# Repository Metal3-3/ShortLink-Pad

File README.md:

# ShortLink-Pad

A hackpad mainly for links and easy accses. Consists of 5 keyswiches 1 rotary encoder for volume controll and ect, one 0.91 inch oled and seeeduino xiao for the micro controller.

# PCB design

it has been designed in kicad and i used the libraries from the guide.

# CAD design

it has been designed in tinkercad and uses m3 screws (3.4mm) might turn out different with other printers
The link: https://www.tinkercad.com/things/gyOfBtvMFHk-hack-pad

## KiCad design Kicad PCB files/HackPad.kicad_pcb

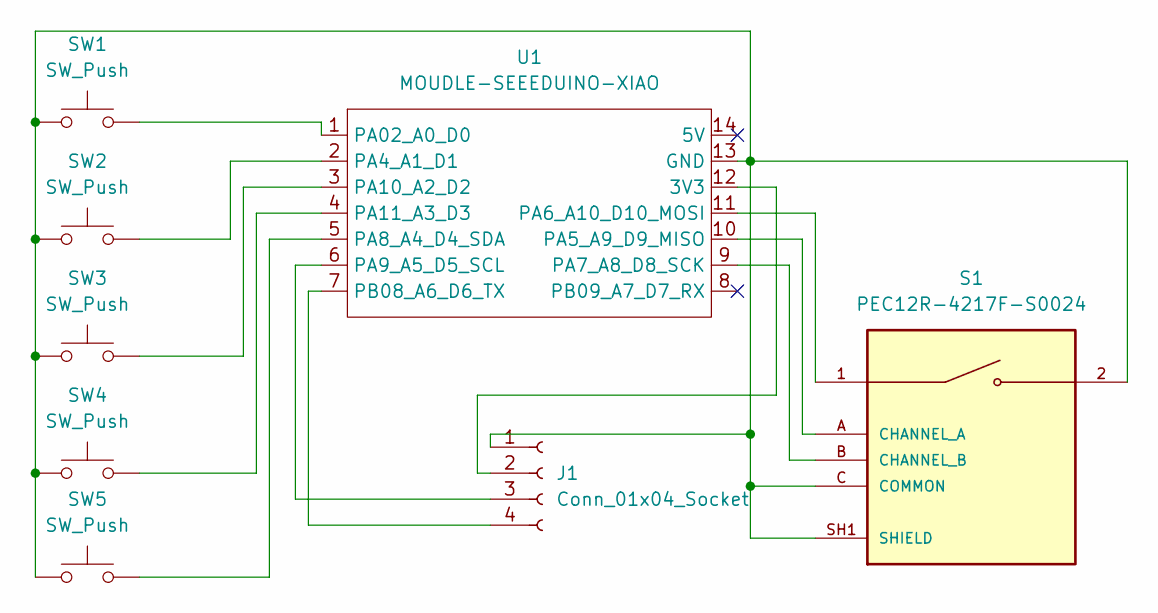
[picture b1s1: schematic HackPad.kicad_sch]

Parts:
J1: Conn_01x04_Socket; SSD1306-0.91-OLED-4pin-128x32
S1: PEC12R-4217F-S0024; XDCR_PEC12R-4217F-S0024; PARTREV 07/21
SW1, SW2, SW3, SW4, SW5: SW_Push; MX-Solderable-1U
U1: MOUDLE-SEEEDUINO-XIAO; XIAO-SAMD21-SMD

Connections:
unnamed: J1.1, S1.2, S1.C (COMMON), S1.SH1 (SHIELD), S1.SH2 (SHIELD), SW1.1, SW2.1, SW3.1, SW4.1, SW5.1, U1.13 (GND)
unnamed: J1.2, U1.12 (3V3)
unnamed: J1.3, U1.6 (PA9_A5_D5_SCL)
unnamed: J1.4, U1.7 (PB08_A6_D6_TX)
unnamed: S1.A (CHANNEL_A), U1.10 (PA5_A9_D9_MISO)
unnamed: S1.B (CHANNEL_B), U1.9 (PA7_A8_D8_SCK)
unnamed: SW1.2, U1.1 (PA02_A0_D0)
unnamed: SW2.2, U1.2 (PA4_A1_D1)
unnamed: S1.1, U1.11 (PA6_A10_D10_MOSI)
unnamed: SW5.2, U1.5 (PA8_A4_D4_SDA)
unnamed: SW3.2, U1.3 (PA10_A2_D2)
unnamed: SW4.2, U1.4 (PA11_A3_D3)

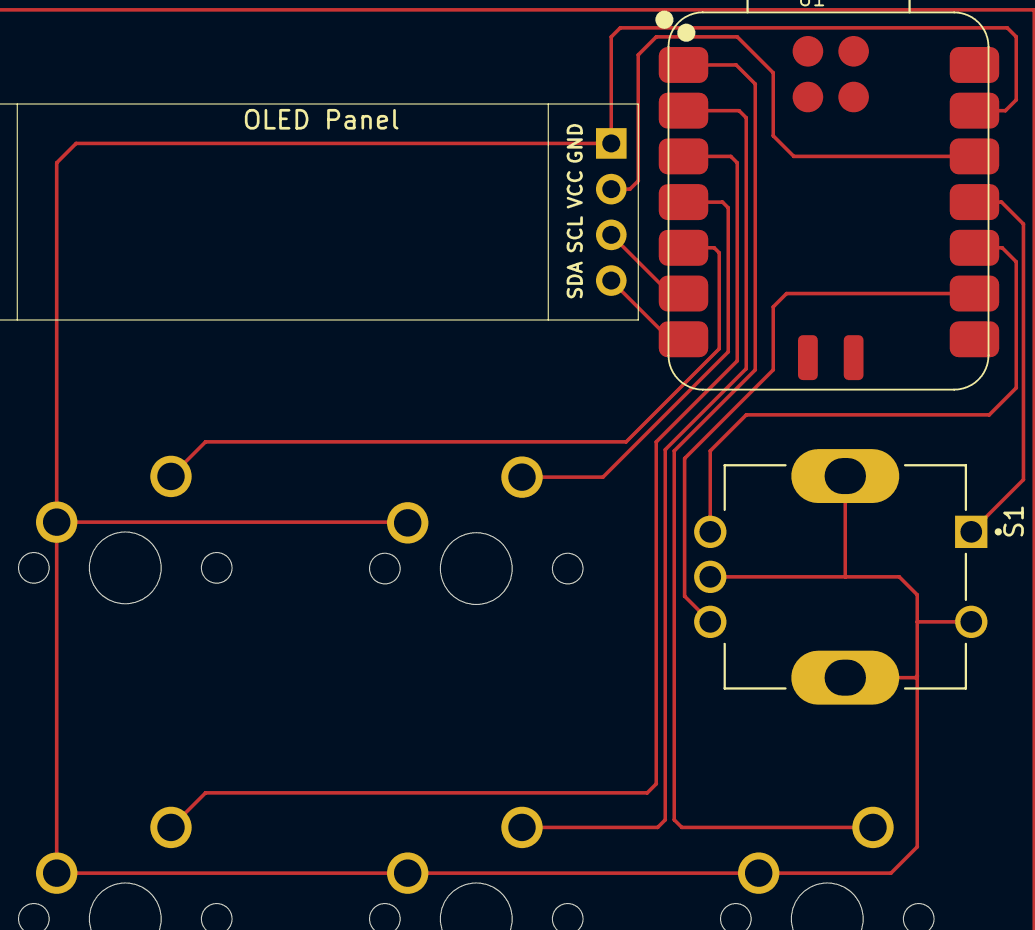
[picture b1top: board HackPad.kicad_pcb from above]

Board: 2 copper layers, 8 parts (0 on the bottom side), 12 nets.
